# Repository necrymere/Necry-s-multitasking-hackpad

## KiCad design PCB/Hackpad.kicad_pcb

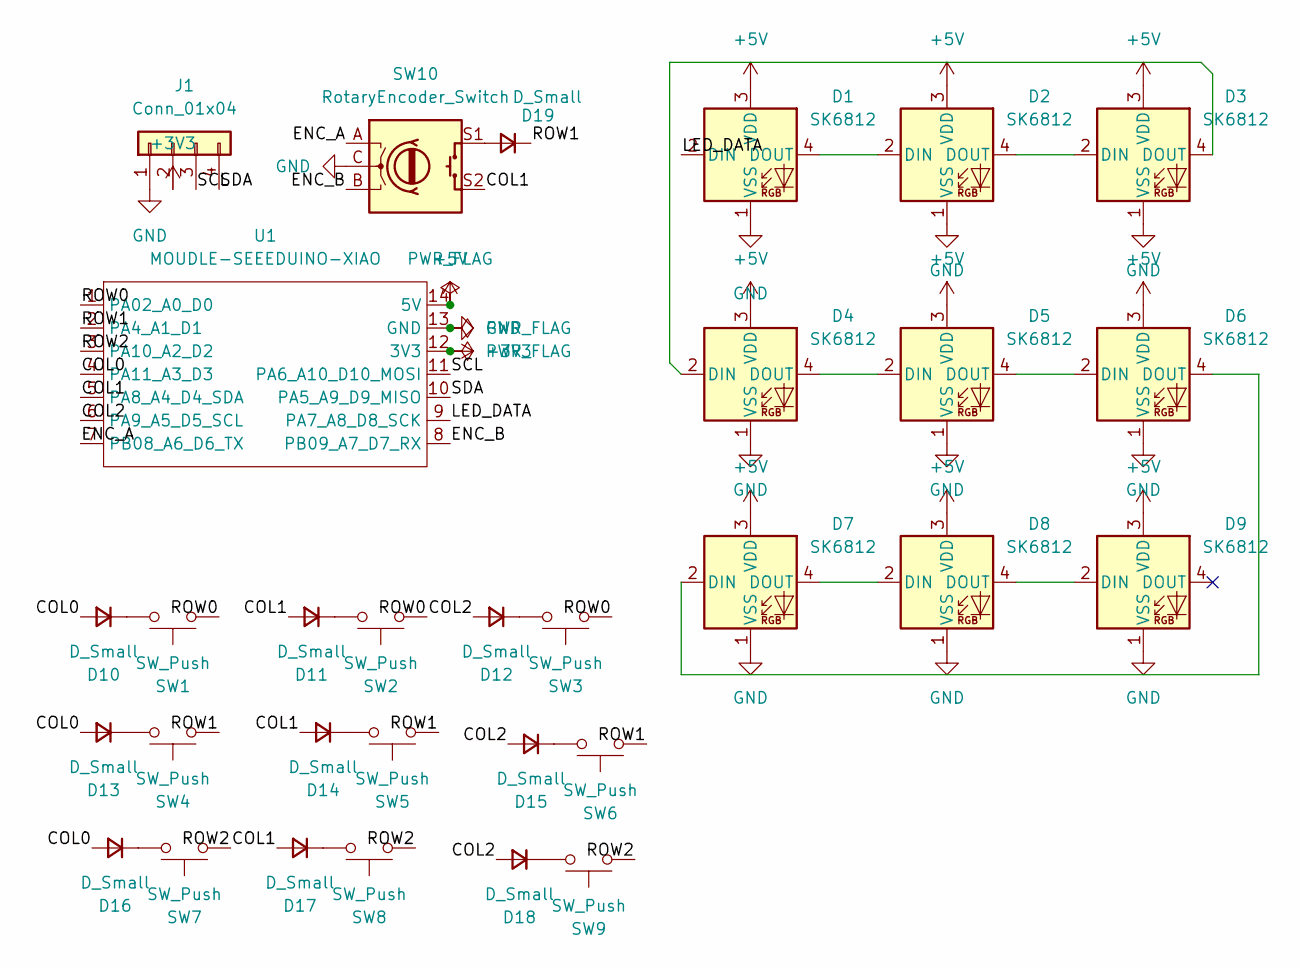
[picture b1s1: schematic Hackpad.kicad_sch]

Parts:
D1, D2, D3, D4, D5, D6, D7, D8, D9: SK6812; LED_SK6812_PLCC4_5.0x5.0mm_P3.2mm
D10, D11, D12, D13, D14, D15, D16, D17, D18, D19: D_Small; D_SOD-123F
J1: Conn_01x04; FanPinHeader_1x04_P2.54mm_Vertical
SW1, SW2, SW3, SW4, SW5, SW6, SW7, SW8, SW9: SW_Push; SW_Cherry_MX_1.00u_PCB
SW10: RotaryEncoder_Switch; RotaryEncoder_Alps_EC11E-Switch_Vertical_H20mm
U1: MOUDLE-SEEEDUINO-XIAO; XIAO-RP2040-DIP

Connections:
+3V3: J1.2, U1.12 (3V3)
+5V: D1.3 (VDD), D2.3 (VDD), D3.3 (VDD), D4.3 (VDD), D5.3 (VDD), D6.3 (VDD), D7.3 (VDD), D8.3 (VDD), D9.3 (VDD), U1.14 (5V)
/COL0: D10.2 (A), D13.2 (A), D16.2 (A), U1.4 (PA11_A3_D3)
/COL1: D11.2 (A), D14.2 (A), D17.2 (A), SW10.S2, U1.5 (PA8_A4_D4_SDA)
/COL2: D12.2 (A), D15.2 (A), D18.2 (A), U1.6 (PA9_A5_D5_SCL)
/ENC_A: SW10.A, U1.7 (PB08_A6_D6_TX)
/ENC_B: SW10.B, U1.8 (PB09_A7_D7_RX)
/LED_DATA: D1.2 (DIN), U1.9 (PA7_A8_D8_SCK)
/ROW0: SW1.1, SW2.1, SW3.1, U1.1 (PA02_A0_D0)
/ROW1: D19.1 (K), SW4.1, SW5.1, SW6.1, U1.2 (PA4_A1_D1)
/ROW2: SW7.1, SW8.1, SW9.1, U1.3 (PA10_A2_D2)
/SCL: J1.3, U1.11 (PA6_A10_D10_MOSI)
/SDA: J1.4, U1.10 (PA5_A9_D9_MISO)
GND: D1.1 (VSS), D2.1 (VSS), D3.1 (VSS), D4.1 (VSS), D5.1 (VSS), D6.1 (VSS), D7.1 (VSS), D8.1 (VSS), D9.1 (VSS), J1.1, SW10.C, U1.13 (GND)
unnamed: D1.4 (DOUT), D2.2 (DIN)
unnamed: D2.4 (DOUT), D3.2 (DIN)
unnamed: D3.4 (DOUT), D4.2 (DIN)
unnamed: D4.4 (DOUT), D5.2 (DIN)
unnamed: D5.4 (DOUT), D6.2 (DIN)
unnamed: D6.4 (DOUT), D7.2 (DIN)
unnamed: D7.4 (DOUT), D8.2 (DIN)
unnamed: D8.4 (DOUT), D9.2 (DIN)
unnamed: D10.1 (K), SW1.2
unnamed: D11.1 (K), SW2.2
unnamed: D12.1 (K), SW3.2
unnamed: D13.1 (K), SW4.2
unnamed: D14.1 (K), SW5.2
unnamed: D15.1 (K), SW6.2
unnamed: D16.1 (K), SW7.2
unnamed: D17.1 (K), SW8.2
unnamed: D18.1 (K), SW9.2
unnamed: D19.2 (A), SW10.S1

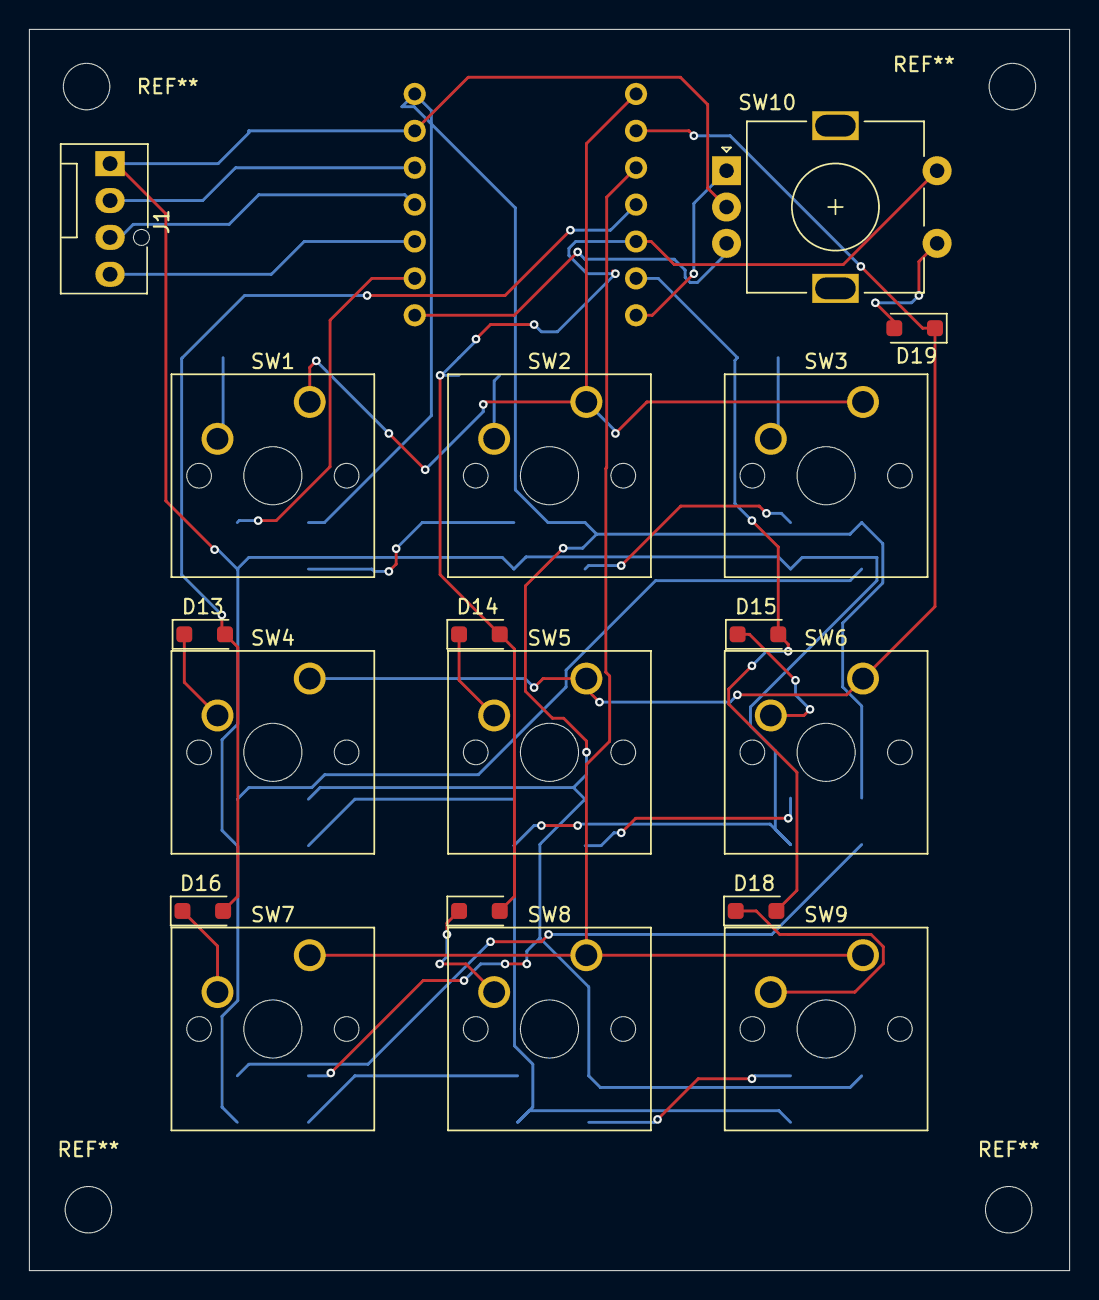
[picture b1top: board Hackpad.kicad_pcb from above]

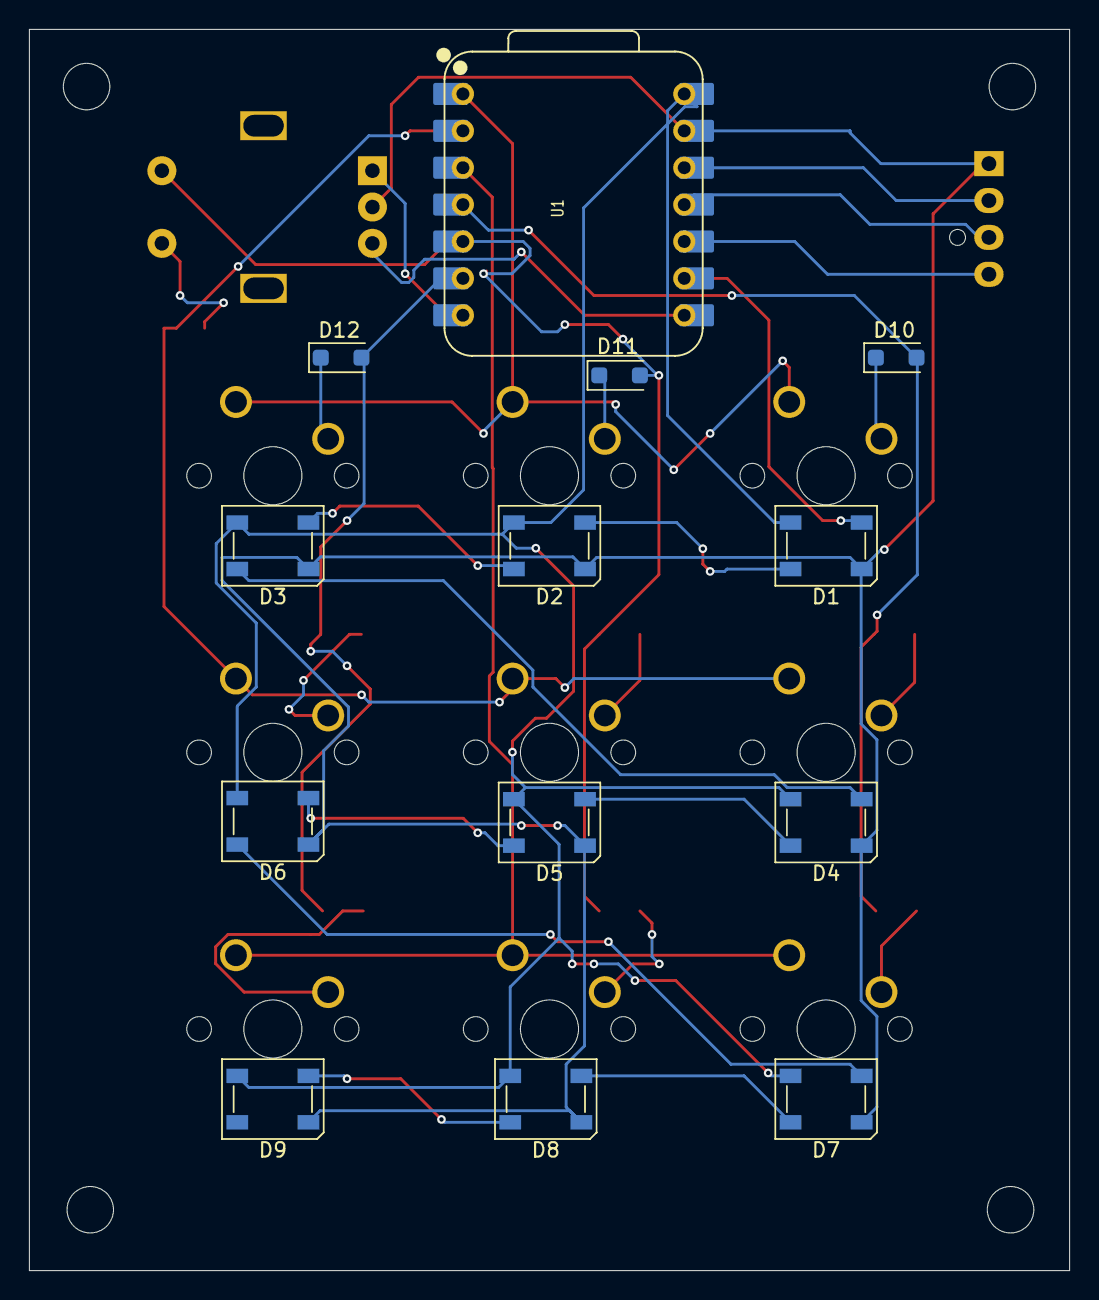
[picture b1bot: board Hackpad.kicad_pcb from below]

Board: 2 copper layers, 71.6 x 85.5 mm, 31 parts (13 on the bottom side), 32 nets.
